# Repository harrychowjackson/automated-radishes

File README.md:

A system for autoamted radish growing.

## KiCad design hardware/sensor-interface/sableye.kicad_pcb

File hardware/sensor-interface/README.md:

Project Sableye - Sensor interface board.
Radishes'n'Bots LLC

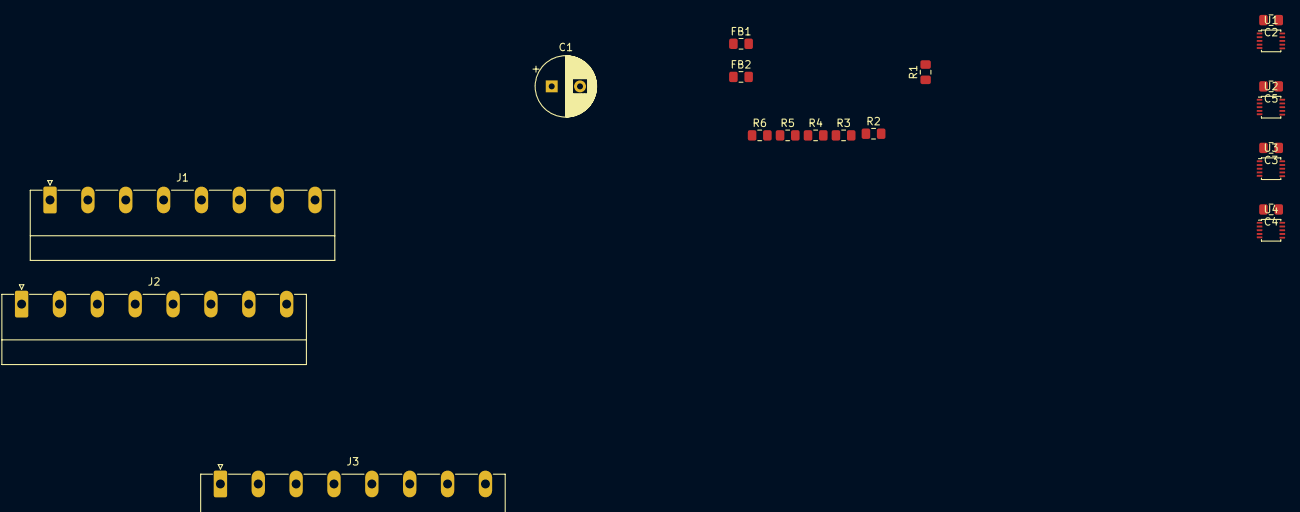
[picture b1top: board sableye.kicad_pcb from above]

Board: 2 copper layers, 20 parts (0 on the bottom side), 26 nets, no tracks yet.

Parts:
C1: 1uF; CP_Radial_D8.0mm_P3.80mm
C2, C3, C4, C5: 1uF; C_0805_2012Metric_Pad1.15x1.40mm_HandSolder
FB1, FB2: MMZ2012Y152B; L_0805_2012Metric_Pad1.15x1.40mm_HandSolder
J1: Conn_PiWR-Pi2C-PiLERTs; PhoenixContact_MC_1,5_8-G-5.08_1x08_P5.08mm_Horizontal
J2: Conn_A0x48-9; PhoenixContact_MC_1,5_8-G-5.08_1x08_P5.08mm_Horizontal
J3: Conn_A0x4A-B; PhoenixContact_MC_1,5_8-G-5.08_1x08_P5.08mm_Horizontal
R1, R2, R3, R4, R5, R6: 10k; R_0805_2012Metric_Pad1.15x1.40mm_HandSolder
U1, U2, U3, U4: ADS1115; VSSOP-10_2.4x2.1mm_P0.5mm

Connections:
ALERT_0x4A: J1.2, R5.2, U3.2
ALERT_0x4B: J1.1, R6.2, U4.2
ALERT_0x48: J1.4, R3.2, U1.2
ALERT_0x49: J1.3, R4.2, U2.2
GND: C2.2, C3.2, C4.2, C5.2, FB2.1, U1.1, U1.3, U2.3, U3.3, U4.3
unnamed: C1.1, FB1.2, J1.8
unnamed: C1.2, FB2.2, J1.6
unnamed: J2.1, U1.4
unnamed: J2.2, U1.5
unnamed: J2.3, U1.6
unnamed: J2.4, U1.7
unnamed: J2.5, U2.4
unnamed: J2.6, U2.5
unnamed: J2.7, U2.6
unnamed: J2.8, U2.7
unnamed: J3.1, U3.4
unnamed: J3.2, U3.5
unnamed: J3.3, U3.6
unnamed: J3.4, U3.7
unnamed: J3.5, U4.4
unnamed: J3.6, U4.5
unnamed: J3.7, U4.6
unnamed: J3.8, U4.7
SCLK: J1.7, R1.2, U1.10, U2.10, U3.1, U3.10, U4.10
SDA: J1.5, R2.2, U1.9, U2.9, U3.9, U4.1, U4.9
VDD: C2.1, C3.1, C4.1, C5.1, FB1.1, R1.1, R2.1, R3.1, R4.1, R5.1, R6.1, U1.8, U2.1, U2.8, U3.8, U4.8

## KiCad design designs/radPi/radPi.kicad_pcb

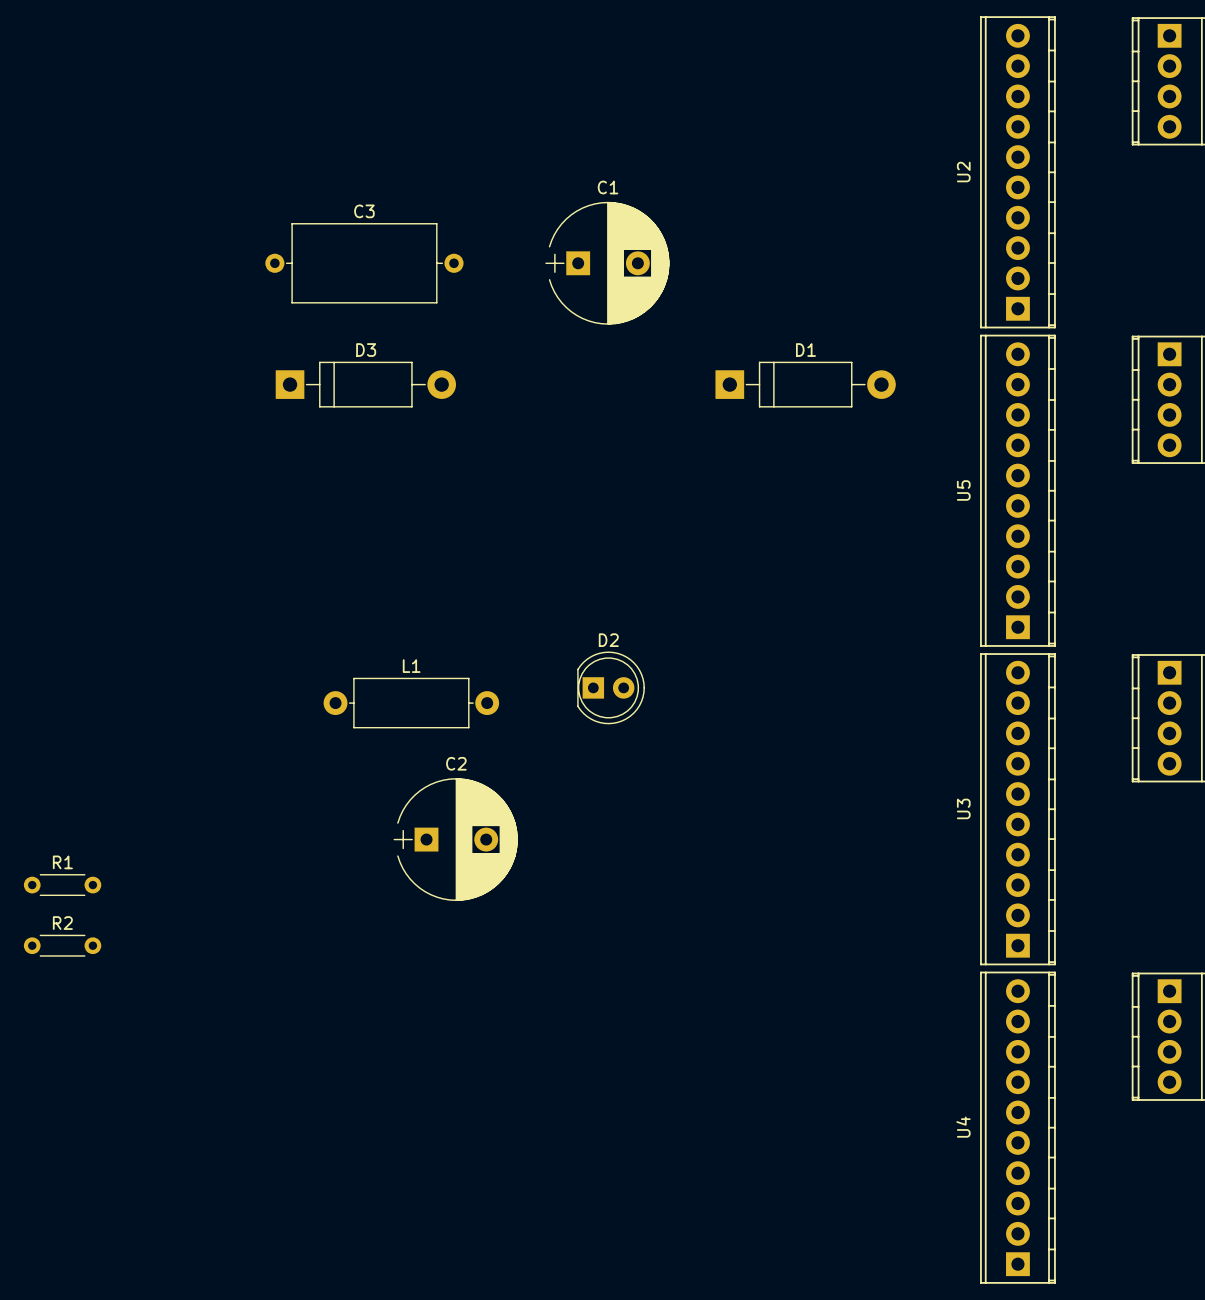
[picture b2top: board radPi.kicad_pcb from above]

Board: 2 copper layers, 17 parts (0 on the bottom side), 26 nets, no tracks yet.

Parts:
C1, C2: CP; CP_Radial_D10.0mm_P5.00mm
C3: 100pF; C_Axial_L12.0mm_D6.5mm_P15.00mm_Horizontal
D1, D3: D; D_DO-15_P12.70mm_Horizontal
D2: LED; LED_D5.0mm
L1: L; L_Axial_L9.5mm_D4.0mm_P12.70mm_Horizontal_Fastron_SMCC
P1, P2, P3, P4: CONN_01X04; TerminalBlock_Pheonix_MPT-2.54mm_4pol
R1: R; R_Axial_DIN0204_L3.6mm_D1.6mm_P5.08mm_Horizontal
R2: 100; R_Axial_DIN0204_L3.6mm_D1.6mm_P5.08mm_Horizontal
U2, U3, U4, U5: ADS1115; TerminalBlock_Pheonix_MPT-2.54mm_10pol

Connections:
+5V: U2.1, U3.1, U4.1, U4.5, U5.1
/Sensor_Interface/ALERT: U2.6, U3.6, U4.6, U5.6
/Sensor_Interface/SCLK: U2.3, U2.5, U3.3, U4.3, U5.3
/Sensor_Interface/SDA: U2.4, U3.4, U4.4, U5.4, U5.5
GND: C1.2, D1.2, L1.1, U2.2, U3.2, U3.5, U4.2, U5.2
GNDD: C2.2, D2.1, L1.2
unnamed: C1.1, D1.1
unnamed: C3.1, D3.1, R2.1
unnamed: C3.2, D3.2
unnamed: D2.2, R2.2
unnamed: P1.1, U3.10
unnamed: P1.2, U3.9
unnamed: P1.3, U3.8
unnamed: P1.4, U3.7
unnamed: P2.1, U4.10
unnamed: P2.2, U4.9
unnamed: P2.3, U4.8
unnamed: P2.4, U4.7
unnamed: P3.1, U5.10
unnamed: P3.2, U5.9
unnamed: P3.3, U5.8
unnamed: P3.4, U5.7
unnamed: P4.1, U2.10
unnamed: P4.2, U2.9
unnamed: P4.3, U2.8
unnamed: P4.4, U2.7

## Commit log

2017-08-28 Initial commit (template).
2017-08-28 Add ADC.
2017-09-08 added test.py to play with picamera. PiCamera can be run in python rather than using that command line stuff we played with before
2017-10-07 updated sensor.py and main.py
2017-10-07 Added camera.py and PCB
2020-01-27 init; working on webcam updates
2020-01-28 usb camera funks; needs polish
2020-02-03 revised sensors
2020-02-07 restructured radishes for nubby branch
2020-02-20 Started re-re-design i2c interface board for fitting more ADCs onboard; needs some more work to accommodate other sensors
